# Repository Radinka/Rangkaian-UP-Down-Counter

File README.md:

# Rangkaian-UP-Down-Counter
Tugas PSE

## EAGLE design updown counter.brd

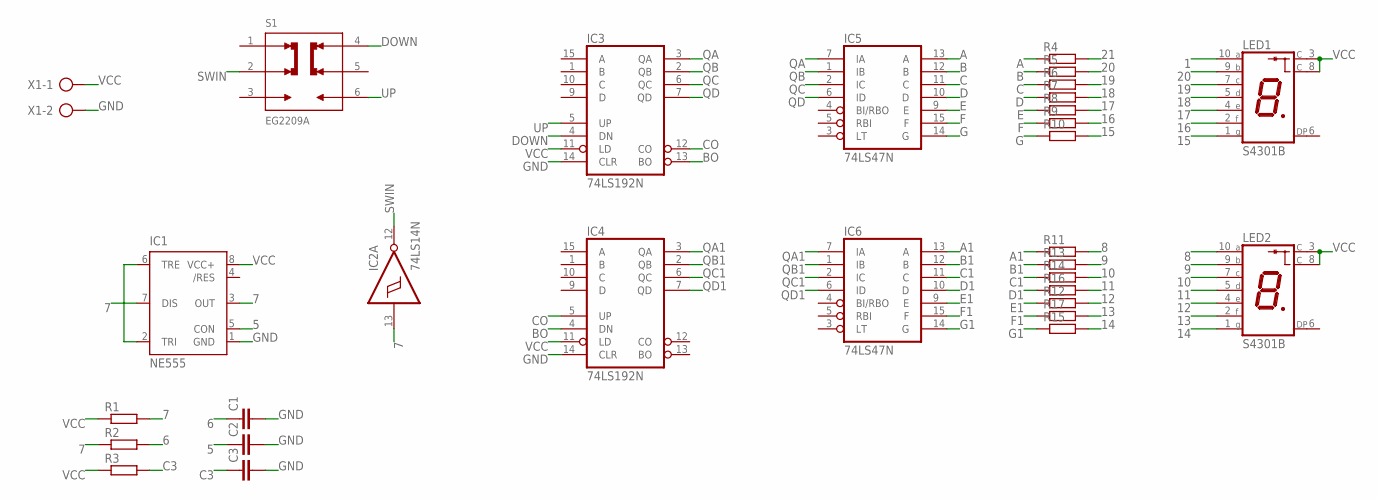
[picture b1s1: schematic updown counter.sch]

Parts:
C1, C2, C3: C-EU025-025X050; C025-025X050
IC1: NE555; DIL-08
IC2: 74LS14N; DIL14
IC3, IC4: 74LS192N; DIL16
IC5, IC6: 74LS47N; DIL16
LED1, LED2: S4301B
R1, R2, R3, R4, R5, R6, R7, R8, R9, R10, R11, R12, R13, R14, R15, R16, R17: R-EU_0207/10; 0207/10
S1: EG2209A; SW_EG2209A
X1: AK300/2

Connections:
1: LED1.10 (A)
5: C2.1, IC1.5 (CON)
6: C1.1, R2.2
7: IC1.3 (OUT), IC1.7 (DIS), IC2.13 (I), R1.2, R2.1
8: LED2.10 (A), R11.2
9: LED2.9 (B), R13.2
10: LED2.7 (C), R14.2
11: LED2.5 (D), R16.2
12: LED2.4 (E), R12.2
13: LED2.2 (F), R17.2
14: LED2.1 (G), R15.2
15: LED1.1 (G), R10.2
16: LED1.2 (F), R9.2
17: LED1.4 (E), R8.2
18: LED1.5 (D), R7.2
19: LED1.7 (C), R6.2
20: LED1.9 (B), R5.2
21: R4.2
A: IC5.13 (A), R4.1
A1: IC6.13 (A), R11.1
B: IC5.12 (B), R5.1
B1: IC6.12 (B), R13.1
BO: IC3.13 (BO), IC4.4 (DN)
C: IC5.11 (C), R6.1
C1: IC6.11 (C), R14.1
C3: C3.1, R3.2
CO: IC3.12 (CO), IC4.5 (UP)
D: IC5.10 (D), R7.1
D1: IC6.10 (D), R16.1
DOWN: IC3.4 (DN), S1.4
E: IC5.9 (E), R8.1
E1: IC6.9 (E), R12.1
F: IC5.15 (F), R9.1
F1: IC6.15 (F), R17.1
G: IC5.14 (G), R10.1
G1: IC6.14 (G), R15.1
GND: C1.2, C2.2, C3.2, IC1.1 (GND), IC2.7 (GND), IC3.8 (GND), IC3.14 (CLR), IC4.8 (GND), IC4.14 (CLR), IC5.8 (GND), IC6.8 (GND), X1.2
unnamed: IC1.2 (TRI), IC1.6 (TRE)
QA: IC3.3 (QA), IC5.7 (IA)
QA1: IC4.3 (QA), IC6.7 (IA)
QB: IC3.2 (QB), IC5.1 (IB)
QB1: IC4.2 (QB), IC6.1 (IB)
QC: IC3.6 (QC), IC5.2 (IC)
QC1: IC4.6 (QC), IC6.2 (IC)
QD: IC3.7 (QD), IC5.6 (ID)
QD1: IC4.7 (QD), IC6.6 (ID)
SWIN: IC2.12 (O), S1.2
UP: IC3.5 (UP), S1.6
VCC: IC1.8 (VCC+), IC2.14 (VCC), IC3.11 (LD), IC3.16 (VCC), IC4.11 (LD), IC4.16 (VCC), IC5.16 (VCC), IC6.16 (VCC), LED1.3 (C), LED1.8 (C), LED2.3 (C), LED2.8 (C), R1.1, R3.1, X1.1

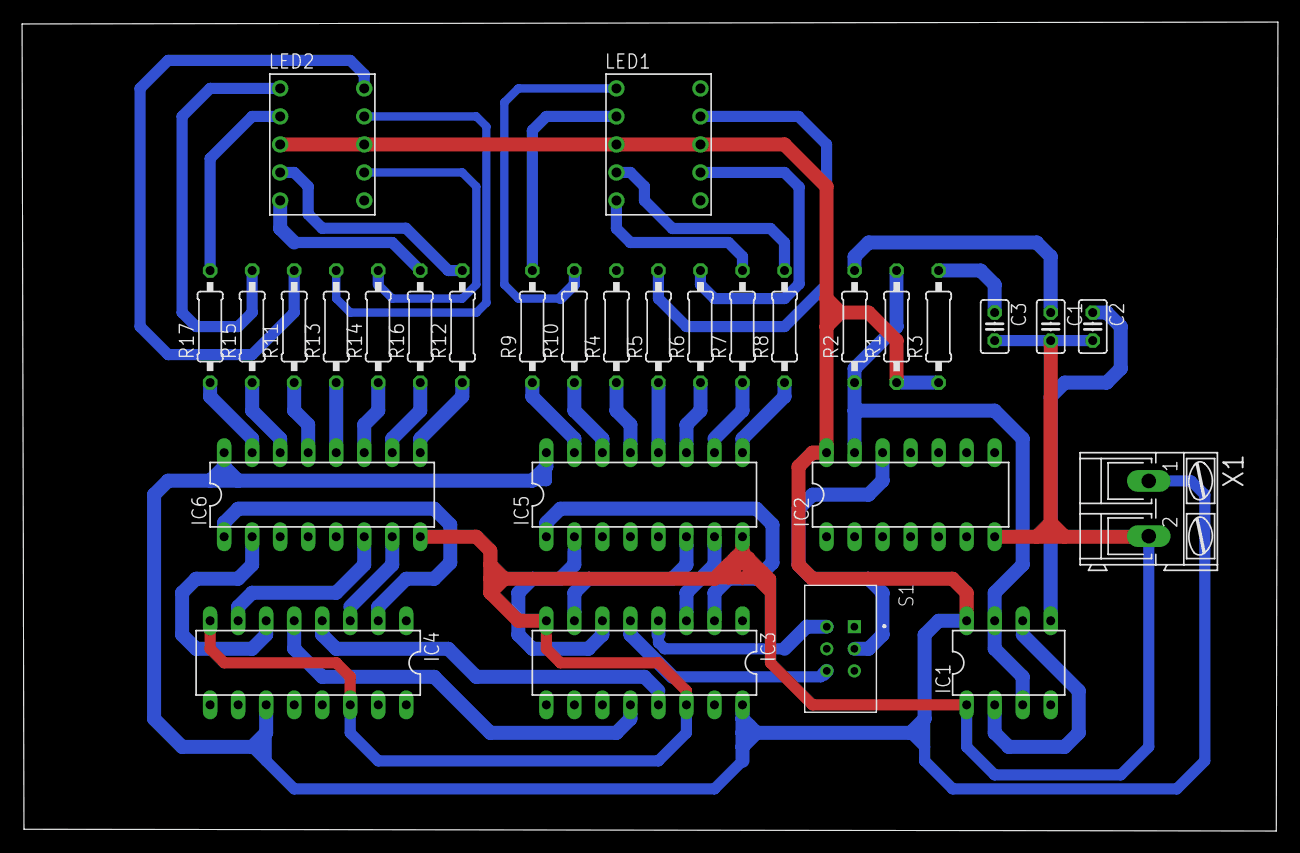
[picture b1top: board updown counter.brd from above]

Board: 2 copper layers, 113.8 x 73.3 mm, 30 parts (0 on the bottom side), 47 nets.
